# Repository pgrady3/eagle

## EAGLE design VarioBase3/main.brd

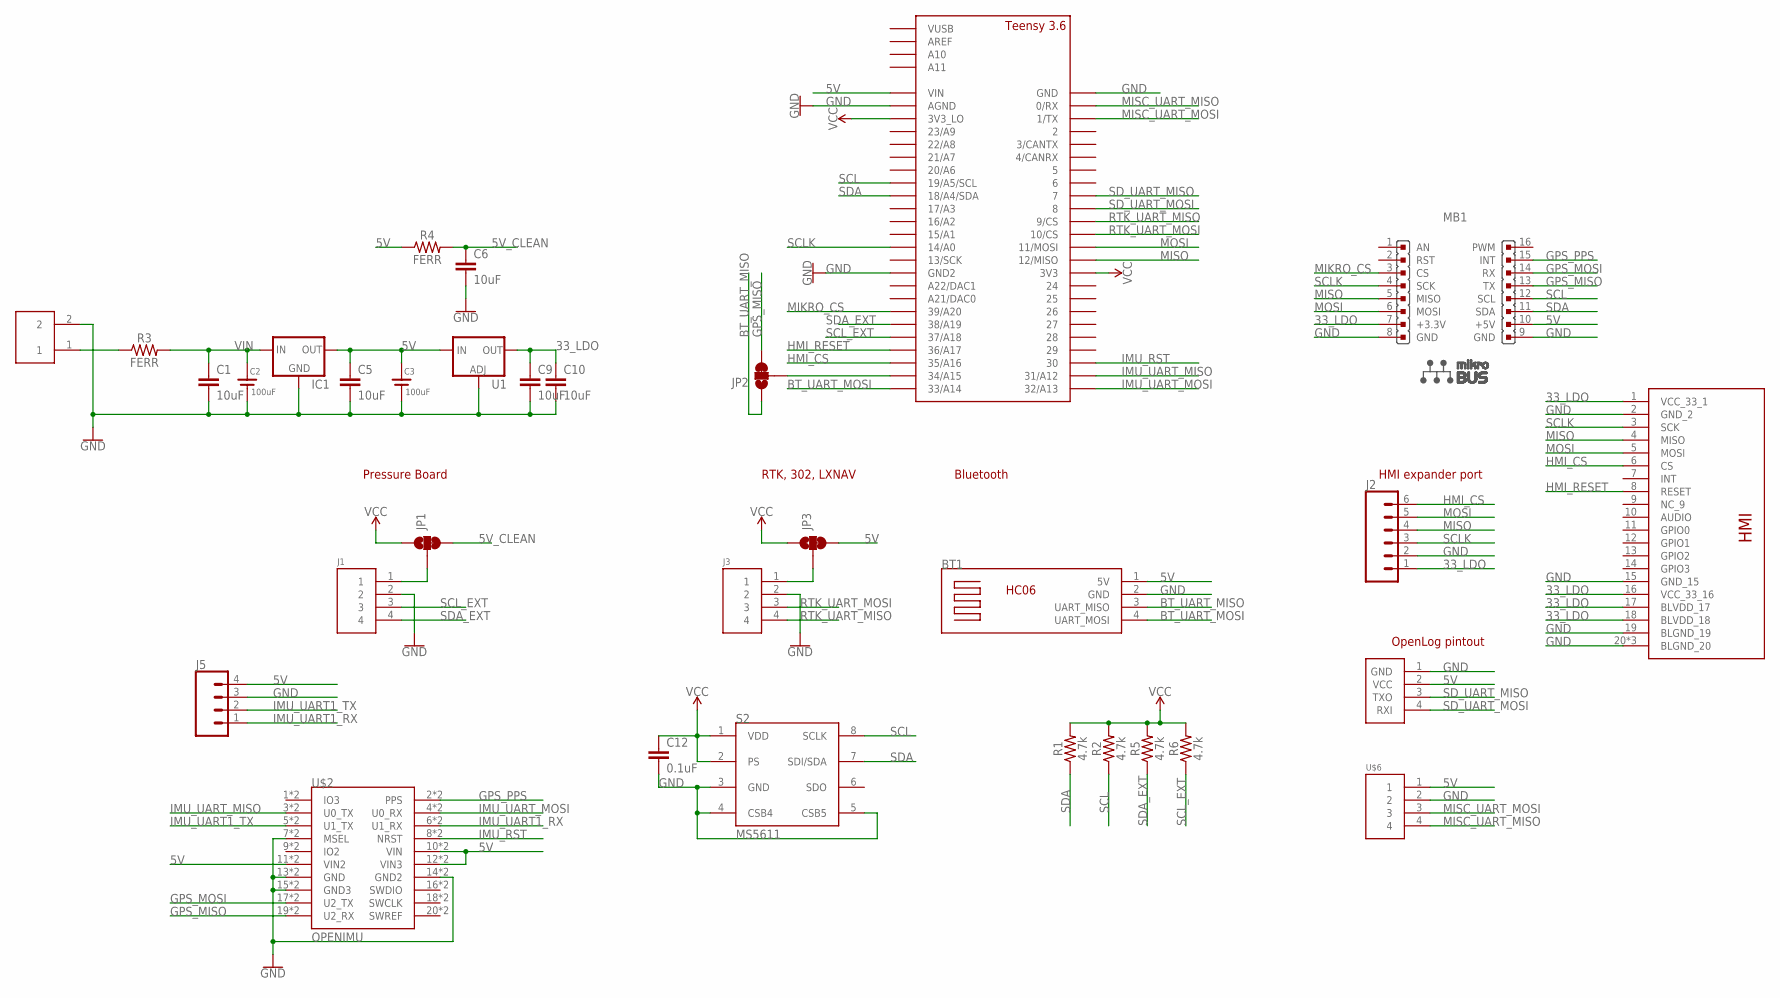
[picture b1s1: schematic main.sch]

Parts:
BT1: HC06
C1, C5, C6, C9, C10: 10uF; 1206
C2, C3: 100uF; CAP_8MM_35MM
C12: 0.1uF; 0603
IC1: V_REG_78XXR-78E; V78W
J1, J3: HEADER4VALULOK; 4PINVALULOK
J2: CONN_06SILK_FEMALE_PTH; 1X06
J5: CONN_04SMD_RA_FEMALE; 1X04_SMD_RA_FEMALE
JP1, JP3: JUMPER-SMT_3_1-NC_TRACE_SILK; SMT-JUMPER_3_1-NC_TRACE_SILK
JP2: JUMPER-SMT_3_1-NC_TRACE_NO-SILK; SMT-JUMPER_3_1-NC_TRACE_NO-SILK
J_PWR: HEADER2; 2PINVALULOK
MB1: MIKROBUS
R1, R2, R5, R6: 4.7k; 0603
R3, R4: FERR; 1206
S2: MS5611
U1: V_REG_317SMD; SOT223
U$1: TEENSY_3.5/3.6_BASIC
U$2: OPENIMU; OPENIMU300ZA
U$4: OPENLOG
U$5: RIVERDI-MATRIX-HMI; FFC-20
U$6: HEADER4VALULOK; 4PINVALULOK

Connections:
5V: BT1.1 (5V), C3.POS (+), C5.1, IC1.OUT, J5.4, JP3.3, MB1.10 (+5V), R4.1, U1.3 (IN), U$1.VIN, U$2.10 (VIN), U$2.11 (VIN2), U$2.12 (VIN3), U$2.H10 (VIN), U$2.H11 (VIN2), U$2.H12 (VIN3), U$4.2 (VCC), U$6.1
5V_CLEAN: C6.1, JP1.3, R4.2
33_LDO: C9.1, C10.1, J2.1, MB1.7 (+3.3V), U1.2 (OUT), U$5.1 (VCC_33_1), U$5.16 (VCC_33_16), U$5.17 (BLVDD_17), U$5.18 (BLVDD_18)
BT_UART_MISO: BT1.3 (UART_MISO), JP2.1
BT_UART_MOSI: BT1.4 (UART_MOSI), U$1.33/A14
GND: BT1.2 (GND), C1.2, C2.NEG (-), C3.NEG (-), C5.2, C6.2, C9.2, C10.2, C12.2, IC1.GND, J1.2, J2.2, J3.2, J5.3, J_PWR.2, MB1.8 (GND), MB1.9 (GND), S2.3 (GND), S2.4 (CSB4), S2.5 (CSB5), U1.1 (ADJ), U$1.AGND, U$1.GND, U$1.GND2, U$2.7 (MSEL), U$2.13 (GND), U$2.14 (GND2), U$2.15 (GND3), U$2.H7 (MSEL), U$2.H13 (GND), U$2.H14 (GND2), U$2.H15 (GND3), U$4.1 (GND), U$5.2 (GND_2), U$5.15 (GND_15), U$5.19 (BLGND_19), U$5.20 (BLGND_20), U$5.PAD1 (BLGND_20), U$5.PAD2 (BLGND_20), U$6.2
GPS_MISO: JP2.3, MB1.13 (TX), U$2.19 (U2_RX), U$2.H19 (U2_RX)
GPS_MOSI: MB1.14 (RX), U$2.17 (U2_TX), U$2.H17 (U2_TX)
GPS_PPS: MB1.15 (INT), U$2.2 (PPS), U$2.H2 (PPS)
HMI_CS: J2.6, U$1.35/A16, U$5.6 (CS)
HMI_RESET: U$1.36/A17, U$5.8 (RESET)
IMU_RST: U$1.30, U$2.8 (NRST), U$2.H8 (NRST)
IMU_UART1_RX: J5.1, U$2.6 (U1_RX), U$2.H6 (U1_RX)
IMU_UART1_TX: J5.2, U$2.5 (U1_TX), U$2.H5 (U1_TX)
IMU_UART_MISO: U$1.31/A12, U$2.3 (U0_TX), U$2.H3 (U0_TX)
IMU_UART_MOSI: U$1.32/A13, U$2.4 (U0_RX), U$2.H4 (U0_RX)
MIKRO_CS: MB1.3 (CS), U$1.39/A20
MISC_UART_MISO: U$1.0/RX, U$6.4
MISC_UART_MOSI: U$1.1/TX, U$6.3
MISO: J2.4, MB1.5 (MISO), U$1.12/MISO, U$5.4 (MISO)
MOSI: J2.5, MB1.6 (MOSI), U$1.11/MOSI, U$5.5 (MOSI)
unnamed: J_PWR.1, R3.1
unnamed: J1.1, JP1.2
unnamed: J3.1, JP3.2
unnamed: JP2.2, U$1.34/A15
RTK_UART_MISO: J3.4, U$1.9/CS
RTK_UART_MOSI: J3.3, U$1.10/CS
SCL: MB1.12 (SCL), R2.1, S2.8 (SCLK), U$1.19/A5/SCL
SCLK: J2.3, MB1.4 (SCK), U$1.14/A0, U$5.3 (SCK)
SCL_EXT: J1.3, R6.1, U$1.37/A18
SDA: MB1.11 (SDA), R1.1, S2.7 (SDI/SDA), U$1.18/A4/SDA
SDA_EXT: J1.4, R5.1, U$1.38/A19
SD_UART_MISO: U$1.7, U$4.3 (TXO)
SD_UART_MOSI: U$1.8, U$4.4 (RXI)
VCC: C12.1, JP1.1, JP3.1, R1.2, R2.2, R5.2, R6.2, S2.1 (VDD), S2.2 (PS), U$1.3V3, U$1.3V3_LO
VIN: C1.1, C2.POS (+), IC1.IN, R3.2

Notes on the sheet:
Pressure Board
RTK, 302, LXNAV
Bluetooth
OpenLog pintout
HMI expander port

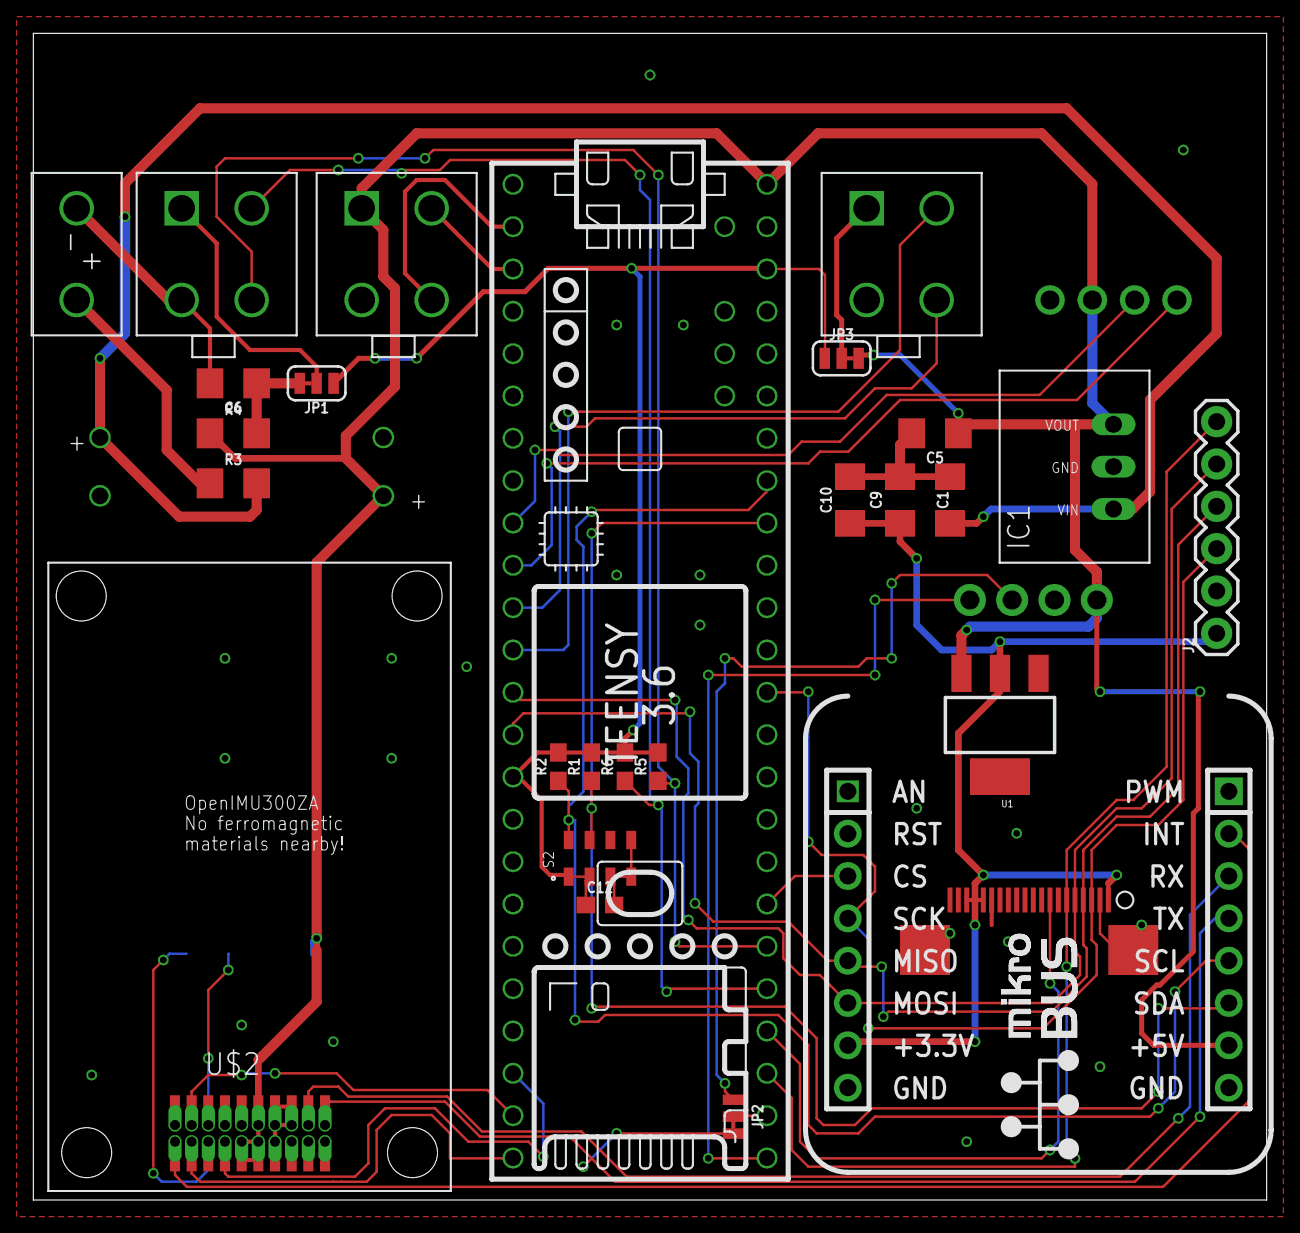
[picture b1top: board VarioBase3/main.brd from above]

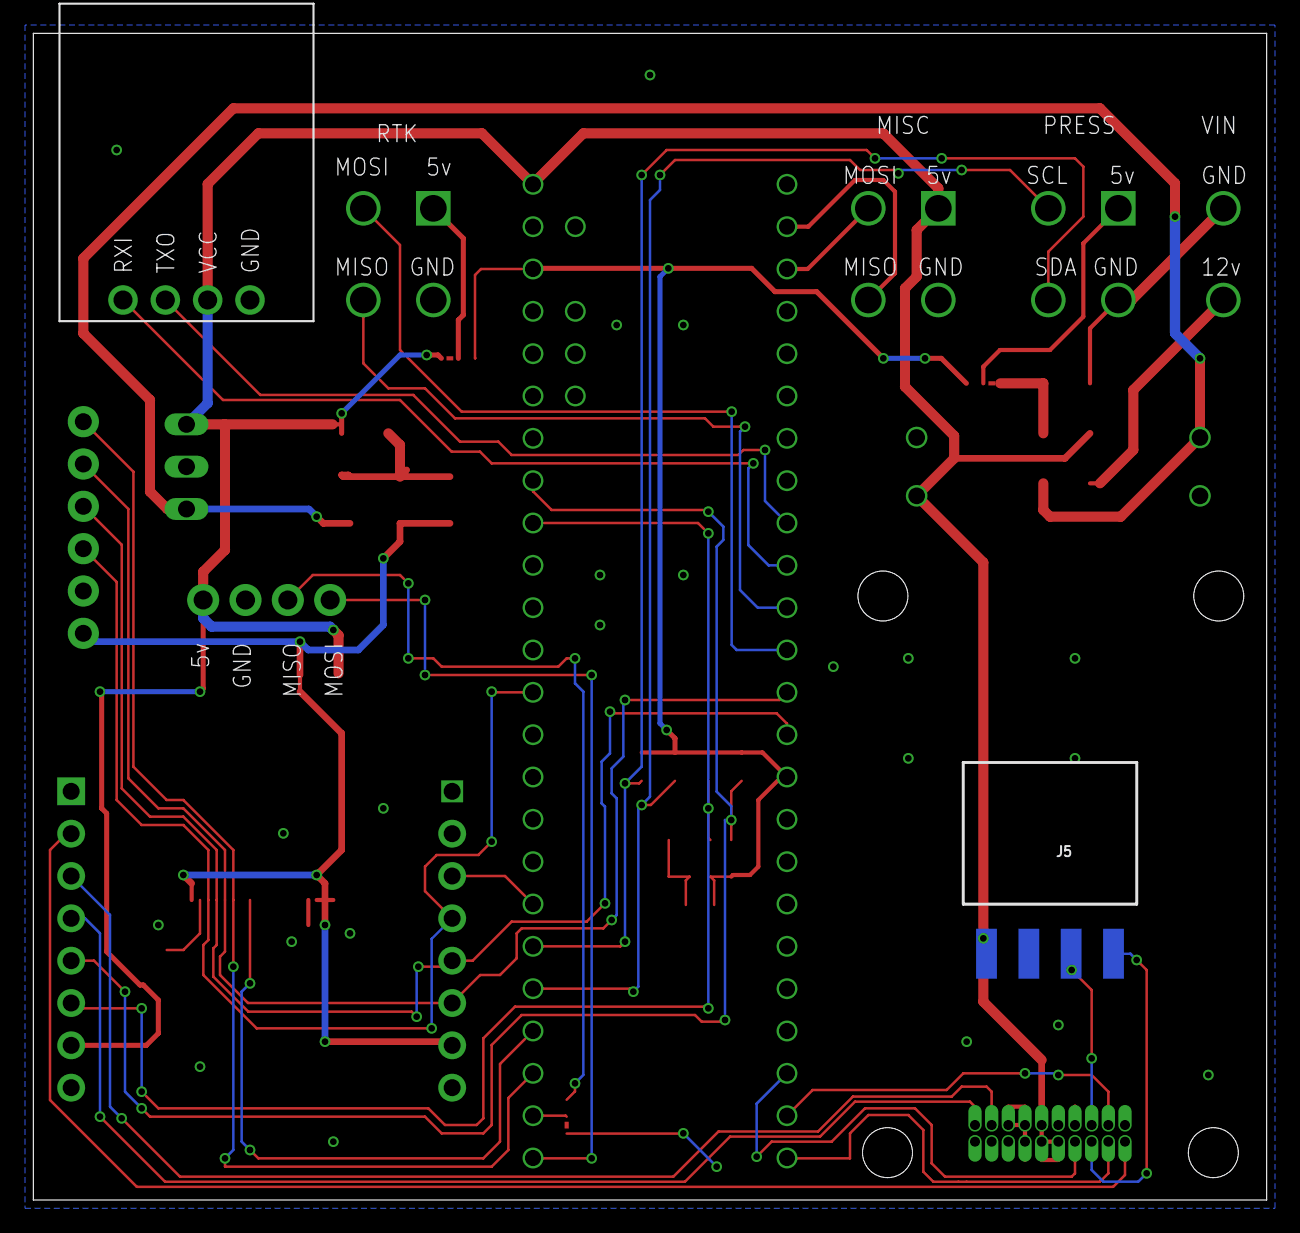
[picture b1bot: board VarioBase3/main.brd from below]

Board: 2 copper layers, 74.0 x 70.0 mm, 32 parts (2 on the bottom side), 36 nets.

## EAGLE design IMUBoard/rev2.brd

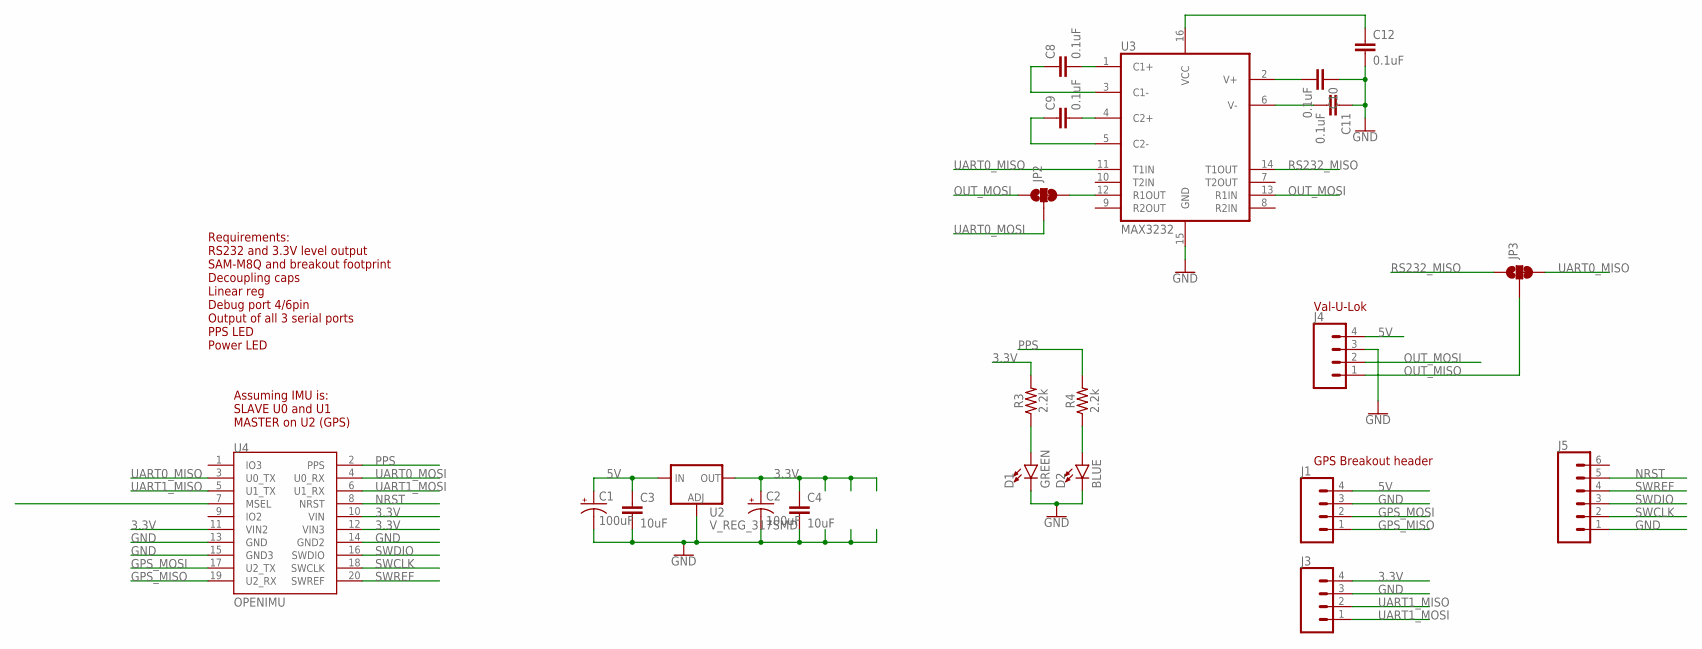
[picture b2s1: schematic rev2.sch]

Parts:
C1, C2: 100uF; EIA3528
C3, C4: 10uF; 0805
C8, C9, C10, C11, C12: 0.1uF; 0603
D1: GREEN; LED-0603
D2: BLUE; LED-0603
J1, J3: CONN_04; 1X04
J4: CONN_04POLAR; MOLEX-1X4
J5: CONN_06POLAR; MOLEX-1X6
JP2, JP3: JUMPER-SMT_3_1-NC_TRACE_SILK; SMT-JUMPER_3_1-NC_TRACE_SILK
R3, R4: 2.2k; 0603
U2: V_REG_317SMD; SOT223
U3: MAX3232; TSSOP16
U4: OPENIMU; OPENIMU300ZA

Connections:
3.3V: C2.A (+), C4.1, J3.4, R3.2, U2.2 (OUT), U4.10 (VIN), U4.11 (VIN2), U4.12 (VIN3)
5V: C1.A (+), C3.1, J1.4, J4.4, U2.3 (IN)
GND: C1.C (-), C2.C (-), C3.2, C4.2, C10.1, C11.1, C12.2, D1.C, D2.C, J1.3, J3.3, J4.3, J5.1, U2.1 (ADJ), U3.15 (GND), U4.13 (GND), U4.14 (GND2), U4.15 (GND3)
GPS_MISO: J1.1, U4.19 (U2_RX)
GPS_MOSI: J1.2, U4.17 (U2_TX)
unnamed: C8.2, U3.1 (C1+)
unnamed: D1.A, R3.1
unnamed: C8.1, U3.3 (C1-)
unnamed: D2.A, R4.1
unnamed: C9.2, U3.4 (C2+)
unnamed: C9.1, U3.5 (C2-)
unnamed: C11.2, U3.6 (V-)
unnamed: C10.2, U3.2 (V+)
unnamed: C12.1, U3.16 (VCC)
unnamed: JP2.3, U3.12 (R1OUT)
NRST: J5.5, U4.8 (NRST)
OUT_MISO: J4.1, JP3.2
OUT_MOSI: J4.2, JP2.1, U3.13 (R1IN)
PPS: R4.2, U4.2 (PPS)
RS232_MISO: JP3.1, U3.14 (T1OUT)
SWCLK: J5.2, U4.18 (SWCLK)
SWDIO: J5.3, U4.16 (SWDIO)
SWREF: J5.4, U4.20 (SWREF)
UART0_MISO: JP3.3, U3.11 (T1IN), U4.3 (U0_TX)
UART0_MOSI: JP2.2, U4.4 (U0_RX)
UART1_MISO: J3.2, U4.5 (U1_TX)
UART1_MOSI: J3.1, U4.6 (U1_RX)

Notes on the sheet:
Requirements: RS232 and 3.3V level output SAM-M8Q and breakout footprint Decoupling caps Linear reg Debug port 4/6pin Output of all 3 serial ports PPS LED Power LED
Val-U-Lok
Assuming IMU is: SLAVE U0 and U1 MASTER on U2 (GPS)
GPS Breakout header

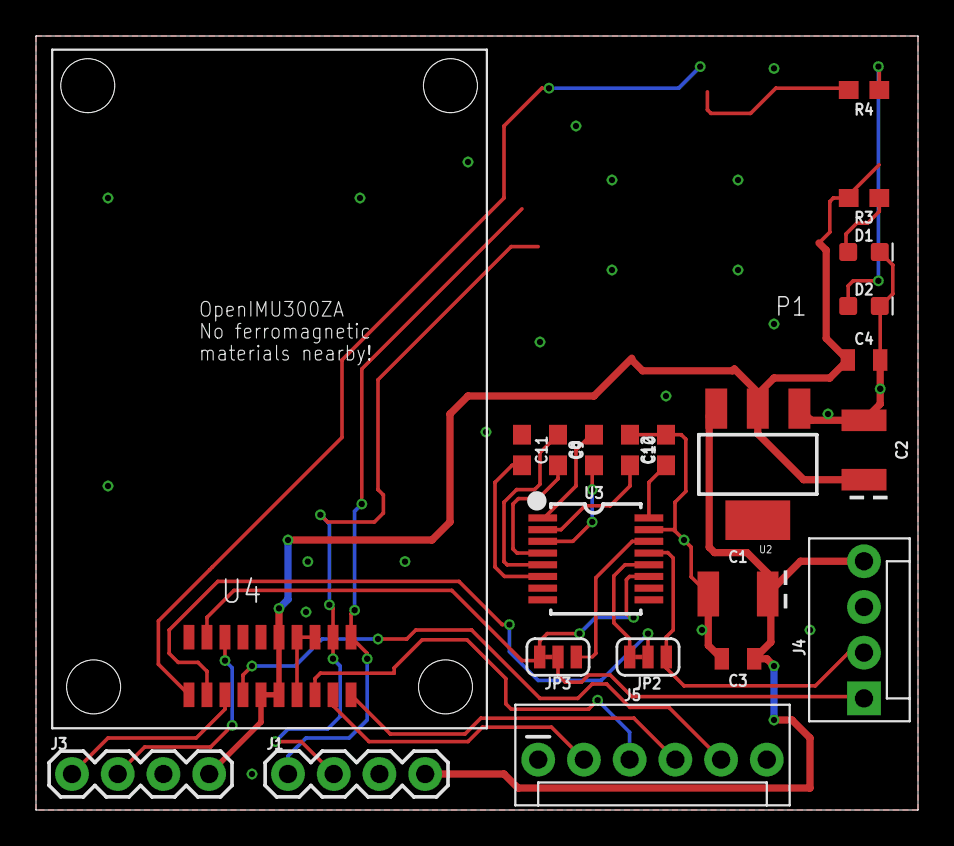
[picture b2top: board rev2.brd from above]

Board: 2 copper layers, 49.0 x 43.0 mm, 22 parts (0 on the bottom side), 27 nets.

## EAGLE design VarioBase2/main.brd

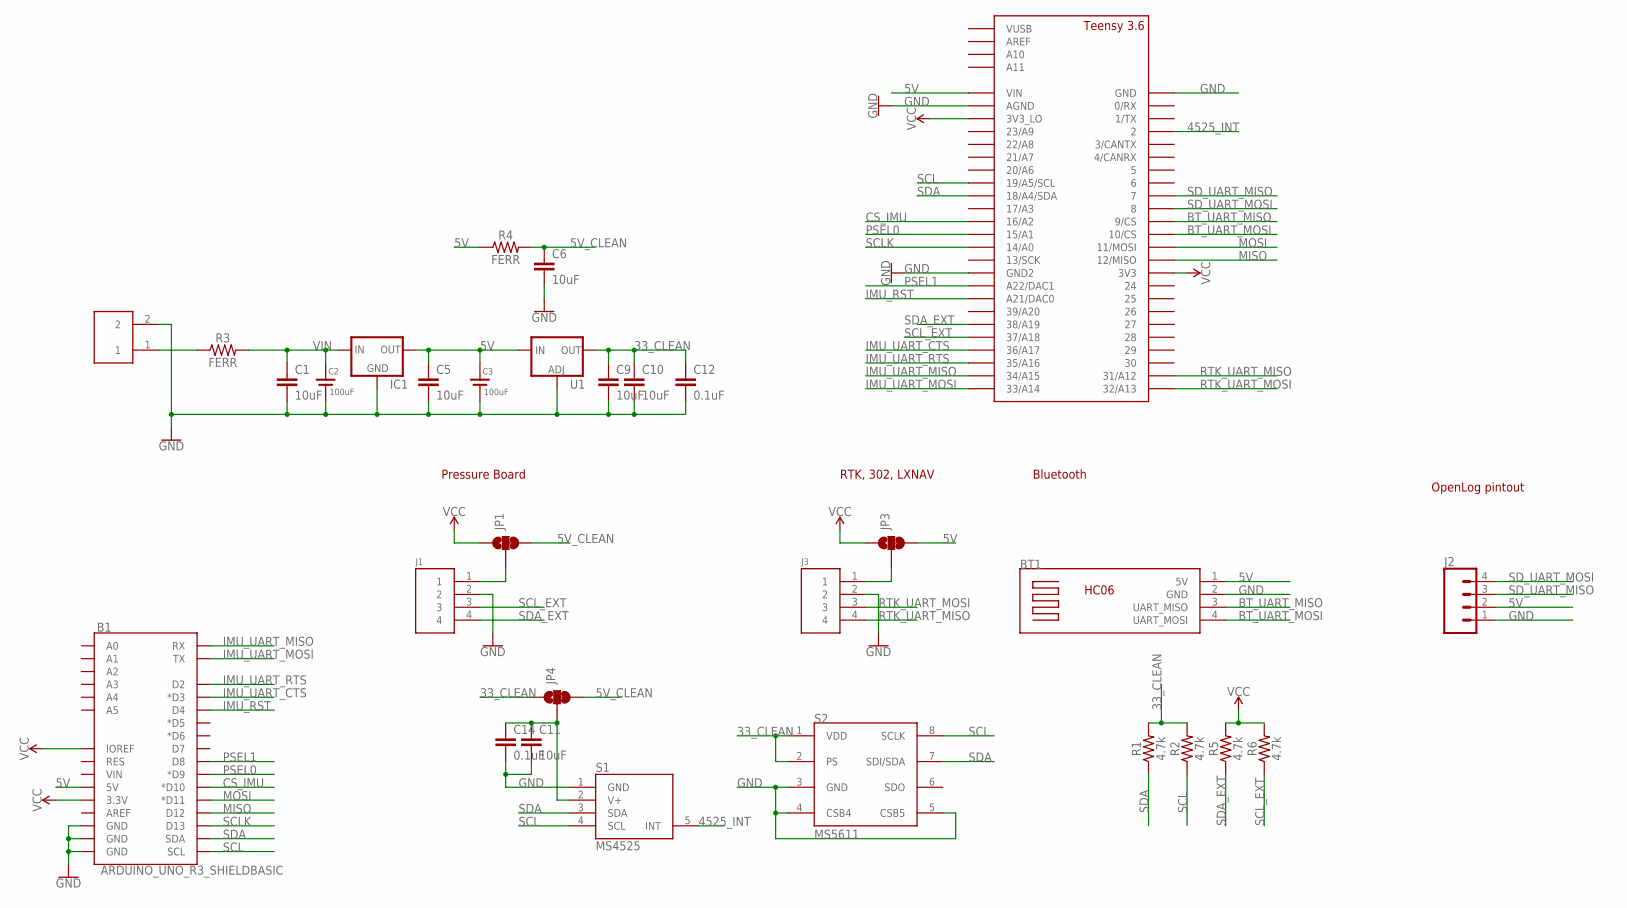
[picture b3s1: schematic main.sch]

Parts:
B1: ARDUINO_UNO_R3_SHIELDBASIC; UNO_R3_SHIELD
BT1: HC06
C1, C5, C6, C9, C10, C11: 10uF; 1206
C2, C3: 100uF; CAP_8MM_35MM
C12, C14: 0.1uF; 0603
IC1: V_REG_78XXR-78E; V78W
J1, J3: HEADER4VALULOK; 4PINVALULOK
J2: CONN_04; 1X04
JP1, JP3, JP4: JUMPER-SMT_3_1-NC_TRACE_SILK; SMT-JUMPER_3_1-NC_TRACE_SILK
R1, R2, R5, R6: 4.7k; 0603
R3, R4: FERR; 1206
S1: MS4525; DIP1270W53P254L990H762Q8B
S2: MS5611
U1: V_REG_317SMD; SOT223
U$1: TEENSY_3.5/3.6_BASIC
U$3: HEADER2; 2PINVALULOK

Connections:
5V: B1.5V, BT1.1 (5V), C3.POS (+), C5.1, IC1.OUT, J2.2, JP3.3, R4.1, U1.3 (IN), U$1.VIN
5V_CLEAN: C6.1, JP1.3, JP4.3, R4.2
33_CLEAN: C9.1, C10.1, C12.1, JP4.1, R1.2, R2.2, S2.1 (VDD), S2.2 (PS), U1.2 (OUT)
4525_INT: S1.5 (INT), U$1.2
BT_UART_MISO: BT1.3 (UART_MISO), U$1.9/CS
BT_UART_MOSI: BT1.4 (UART_MOSI), U$1.10/CS
CS_IMU: B1.D10 (*D10), U$1.16/A2
GND: B1.GND@0 (GND), B1.GND@1 (GND), B1.GND@2 (GND), BT1.2 (GND), C1.2, C2.NEG (-), C3.NEG (-), C5.2, C6.2, C9.2, C10.2, C11.2, C12.2, C14.2, IC1.GND, J1.2, J2.1, J3.2, S1.1 (GND), S2.3 (GND), S2.4 (CSB4), S2.5 (CSB5), U1.1 (ADJ), U$1.AGND, U$1.GND, U$1.GND2, U$3.2
IMU_RST: B1.D4, U$1.21/DAC0 (A21/DAC0)
IMU_UART_CTS: B1.D3 (*D3), U$1.36/A17
IMU_UART_MISO: B1.RX, U$1.34/A15
IMU_UART_MOSI: B1.TX, U$1.33/A14
IMU_UART_RTS: B1.D2, U$1.35/A16
MISO: B1.D12, U$1.12/MISO
MOSI: B1.D11 (*D11), U$1.11/MOSI
unnamed: R3.1, U$3.1
unnamed: J1.1, JP1.2
unnamed: J3.1, JP3.2
unnamed: C11.1, C14.1, JP4.2, S1.2 (V+)
PSEL0: B1.D9 (*D9), U$1.15/A1
PSEL1: B1.D8, U$1.A22/DAC1
RTK_UART_MISO: J3.4, U$1.31/A12
RTK_UART_MOSI: J3.3, U$1.32/A13
SCL: B1.SCL, R2.1, S1.4 (SCL), S2.8 (SCLK), U$1.19/A5/SCL
SCLK: B1.D13, U$1.14/A0
SCL_EXT: J1.3, R6.1, U$1.37/A18
SDA: B1.SDA, R1.1, S1.3 (SDA), S2.7 (SDI/SDA), U$1.18/A4/SDA
SDA_EXT: J1.4, R5.1, U$1.38/A19
SD_UART_MISO: J2.3, U$1.7
SD_UART_MOSI: J2.4, U$1.8
VCC: B1.3.3V, B1.IOREF, JP1.1, JP3.1, R5.2, R6.2, U$1.3V3, U$1.3V3_LO
VIN: C1.1, C2.POS (+), IC1.IN, R3.2

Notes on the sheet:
Pressure Board
RTK, 302, LXNAV
Bluetooth
OpenLog pintout

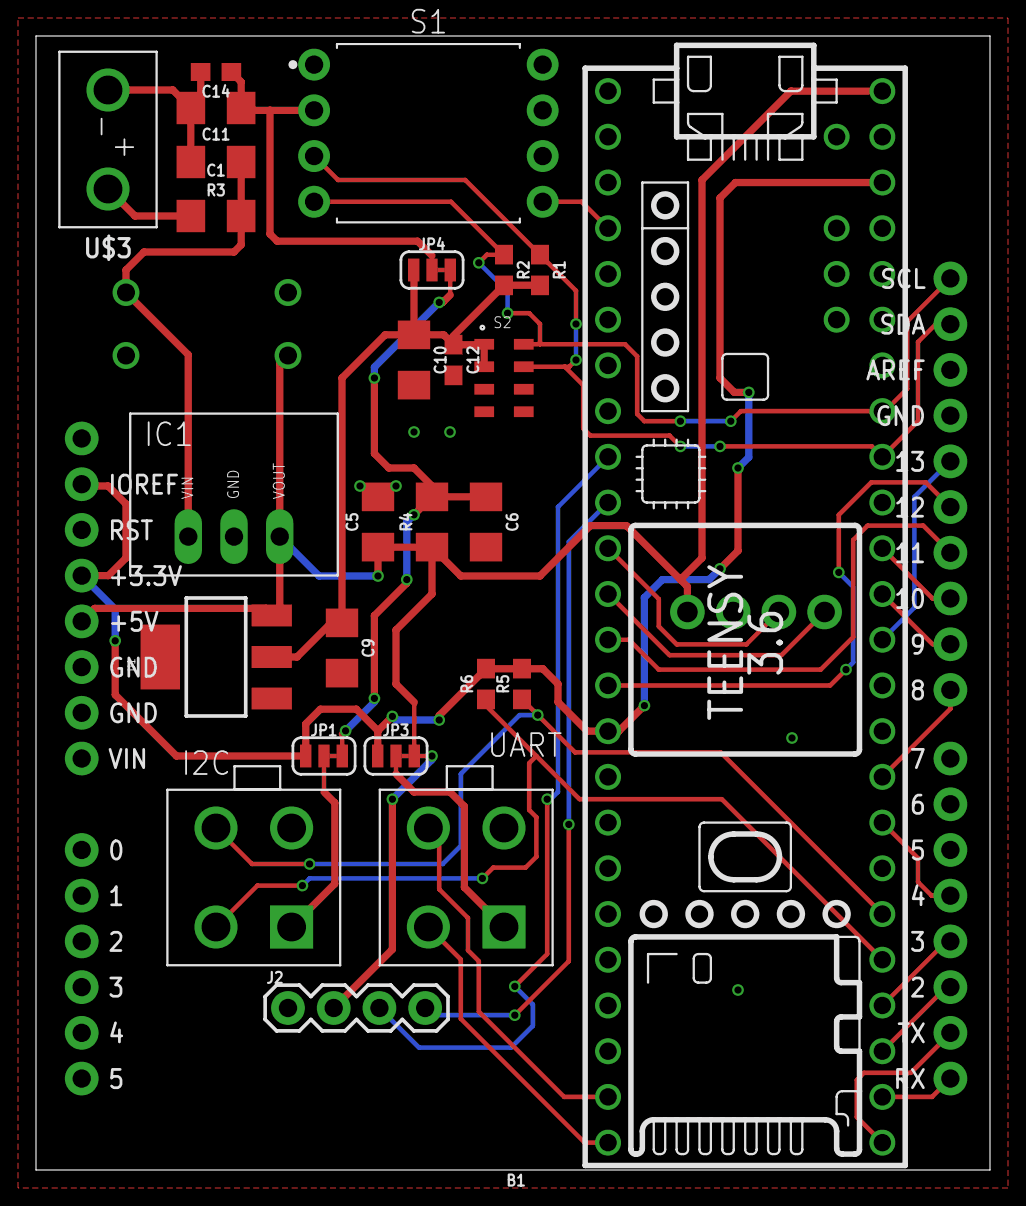
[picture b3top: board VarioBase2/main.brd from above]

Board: 2 copper layers, 53.0 x 63.0 mm, 30 parts (1 on the bottom side), 32 nets.

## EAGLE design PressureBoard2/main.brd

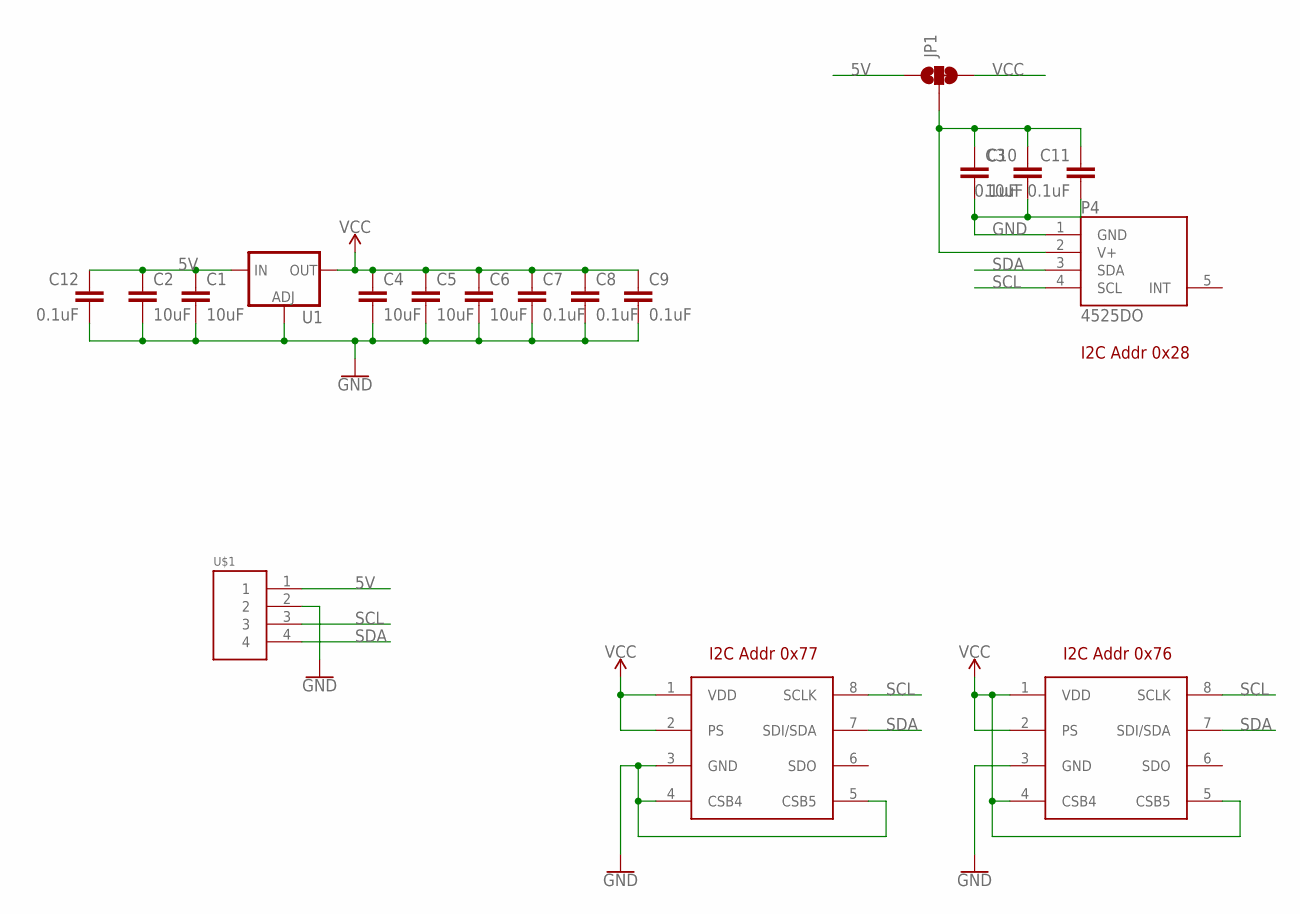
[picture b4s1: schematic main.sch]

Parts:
C1, C2, C3, C4, C5, C6: 10uF; 0805
C7, C8, C9, C10, C11, C12: 0.1uF; 0603
JP1: JUMPER-SMT_3_1-NC_TRACE_NO-SILK; SMT-JUMPER_3_1-NC_TRACE_NO-SILK
P1, P2: MS5611
P4: 4525DO; DIP1270W53P254L990H762Q8B
U1: V_REG_317SMD; SOT223
U$1: HEADER4VALULOK; 4PINVALULOK

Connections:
5V: C1.1, C2.1, C12.1, JP1.1, U1.3 (IN), U$1.1
GND: C1.2, C2.2, C3.2, C4.2, C5.2, C6.2, C7.2, C8.2, C9.2, C10.2, C11.2, C12.2, P1.3 (GND), P1.4 (CSB4), P1.5 (CSB5), P2.3 (GND), P4.1 (GND), U1.1 (ADJ), U$1.2
unnamed: C3.1, C10.1, C11.1, JP1.2, P4.2 (V+)
SCL: P1.8 (SCLK), P2.8 (SCLK), P4.4 (SCL), U$1.3
SDA: P1.7 (SDI/SDA), P2.7 (SDI/SDA), P4.3 (SDA), U$1.4
VCC: C4.1, C5.1, C6.1, C7.1, C8.1, C9.1, JP1.3, P1.1 (VDD), P1.2 (PS), P2.1 (VDD), P2.2 (PS), P2.4 (CSB4), P2.5 (CSB5), U1.2 (OUT)

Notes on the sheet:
I2C Addr 0x28
I2C Addr 0x77
I2C Addr 0x76

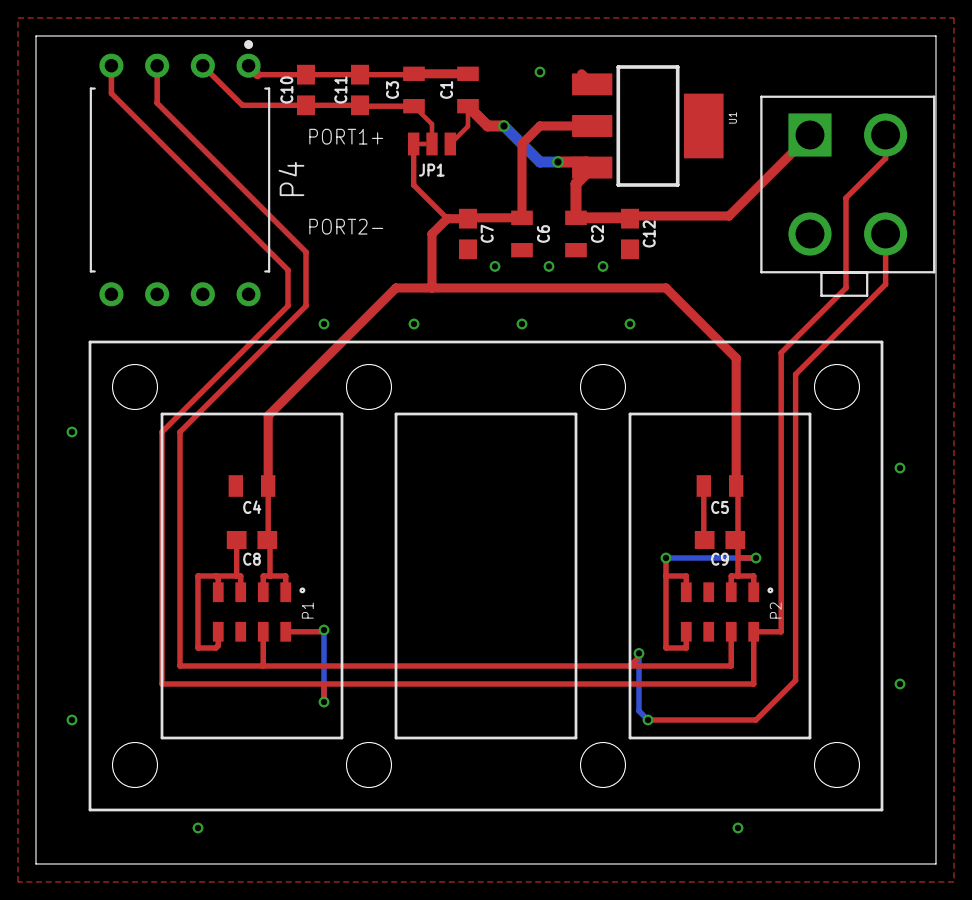
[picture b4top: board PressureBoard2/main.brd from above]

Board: 2 copper layers, 50.0 x 46.0 mm, 18 parts (0 on the bottom side), 6 nets.

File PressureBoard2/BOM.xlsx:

Digikey part # | Designator | Qty | Price | Description
AZ1117EH-3.3TRG1DICT-ND | U1 | 1 | 0.32 | Linear 3.3 reg |  |  |  | 0.32 |  | 64.25
1276-6455-1-ND | C1,C2,C3,C4,C5,C6 | 6 | 0.1 | 10uF cap |  |  |  | 0.60000000000000009
1276-1000-1-ND | C7,C8,C9 | 3 | 0.01 | 0.1uF cap |  |  |  | 0.03
2057-ICS-308-T-ND |  |  |  | 8 DIP socket |  |  |  | 0
223-1622-1-ND |  | 2 | 12.4 | MS5611 |  |  |  | 24.8
223-1110-ND |  | 1 | 38.5 | 4525DO |  |  |  | 38.5
 |  |  |  |  |  |  |  | 0
EB50 |  | 3 |  | 3/16 to 10-32 conn |  |  |  | 0
EB25 |  | 2 |  | 3/32 to 10-32 conn |  |  |  | 0
 |  |  |  |  |  |  |  | 0
 |  |  |  |  |  |  |  | 0
 |  |  |  |  |  |  |  | 0
 |  |  |  |  |  |  |  | 0
 |  |  |  |  |  |  |  | 0
 |  |  |  |  |  |  |  | 0
 |  |  |  |  |  |  |  | 0
 |  |  |  |  |  |  |  | 0
 |  |  |  |  |  |  |  | 0

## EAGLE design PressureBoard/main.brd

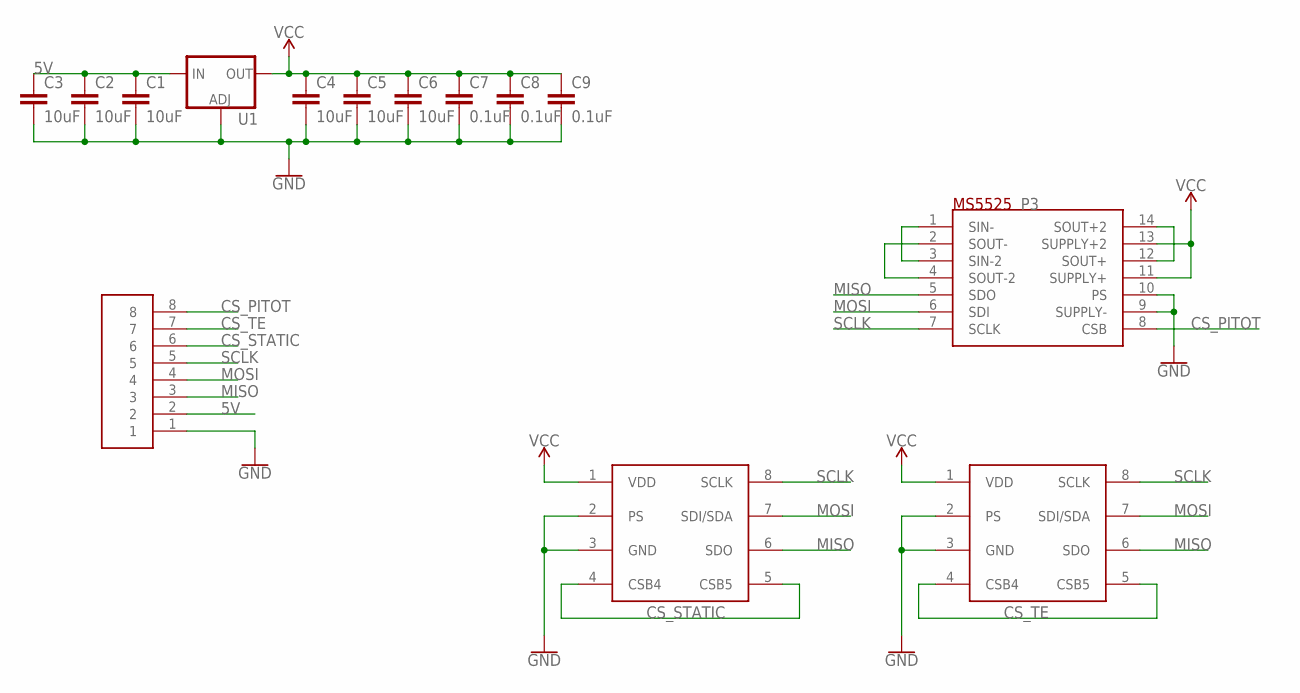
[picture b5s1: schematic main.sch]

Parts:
C1, C2, C3, C4, C5, C6: 10uF; 0805
C7, C8, C9: 0.1uF; 0603
P1, P2: MS5611
P3: MS5525; SOIC14-WIDE
U1: V_REG_317SMD; SOT223
U$1: HEADER8; 8PINVALULOK

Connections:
5V: C1.1, C2.1, C3.1, U1.3 (IN), U$1.2
CS_PITOT: P3.8 (CSB), U$1.8
CS_STATIC: P1.4 (CSB4), P1.5 (CSB5), U$1.6
CS_TE: P2.4 (CSB4), P2.5 (CSB5), U$1.7
GND: C1.2, C2.2, C3.2, C4.2, C5.2, C6.2, C7.2, C8.2, C9.2, P1.2 (PS), P1.3 (GND), P2.2 (PS), P2.3 (GND), P3.9 (SUPPLY-), P3.10 (PS), U1.1 (ADJ), U$1.1
MISO: P1.6 (SDO), P2.6 (SDO), P3.5 (SDO), U$1.3
MOSI: P1.7 (SDI/SDA), P2.7 (SDI/SDA), P3.6 (SDI), U$1.4
unnamed: P3.1 (SIN-), P3.3 (SIN-2)
unnamed: P3.2 (SOUT-), P3.4 (SOUT-2)
unnamed: P3.12 (SOUT+), P3.14 (SOUT+2)
SCLK: P1.8 (SCLK), P2.8 (SCLK), P3.7 (SCLK), U$1.5
VCC: C4.1, C5.1, C6.1, C7.1, C8.1, C9.1, P1.1 (VDD), P2.1 (VDD), P3.11 (SUPPLY+), P3.13 (SUPPLY+2), U1.2 (OUT)

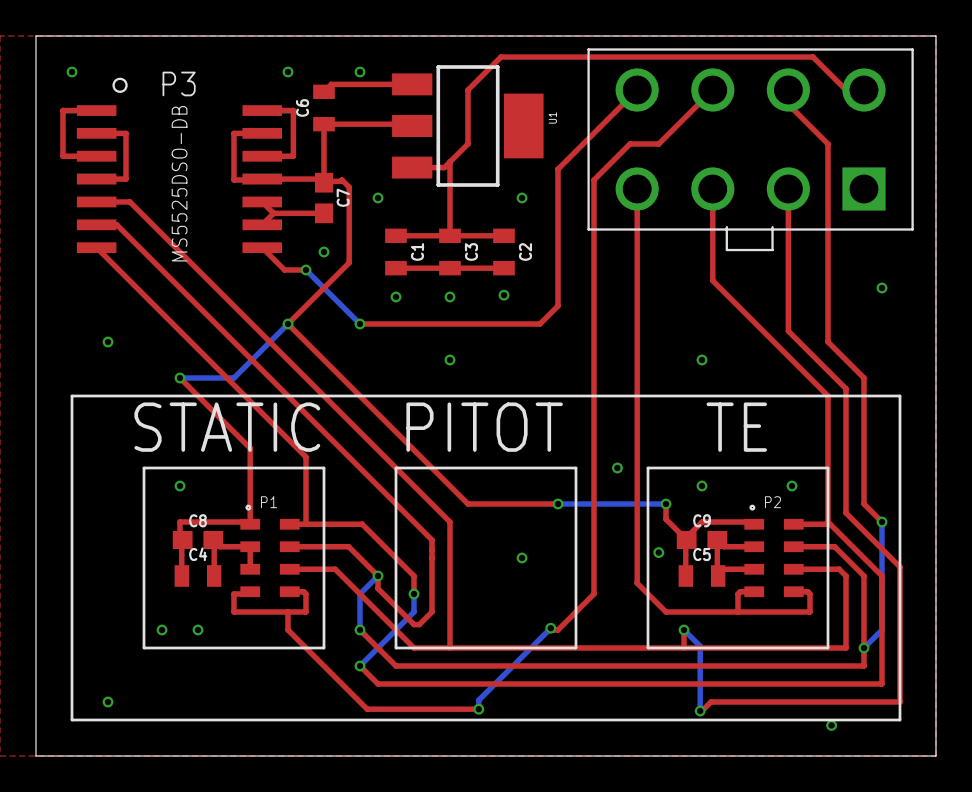
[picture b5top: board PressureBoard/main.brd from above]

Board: 2 copper layers, 50.0 x 40.0 mm, 14 parts (0 on the bottom side), 12 nets.

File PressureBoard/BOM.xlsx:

Digikey part # | Designator | Qty | Price | Description
AZ1117EH-3.3TRG1DICT-ND | U1 | 1 | 0.32 | Linear 3.3 reg |  |  |  | 0.32 |  | 0.95000000000000018
1276-6455-1-ND | C1,C2,C3,C4,C5,C6 | 6 | 0.1 | 10uF cap |  |  |  | 0.60000000000000009
1276-1000-1-ND | C7,C8,C9 | 3 | 0.01 | 0.1uF cap |  |  |  | 0.03
 |  |  |  |  |  |  |  | 0
 |  |  |  |  |  |  |  | 0
 |  |  |  |  |  |  |  | 0
 |  |  |  |  |  |  |  | 0
 |  |  |  |  |  |  |  | 0
 |  |  |  |  |  |  |  | 0
 |  |  |  |  |  |  |  | 0
 |  |  |  |  |  |  |  | 0
 |  |  |  |  |  |  |  | 0
 |  |  |  |  |  |  |  | 0
 |  |  |  |  |  |  |  | 0
 |  |  |  |  |  |  |  | 0
 |  |  |  |  |  |  |  | 0

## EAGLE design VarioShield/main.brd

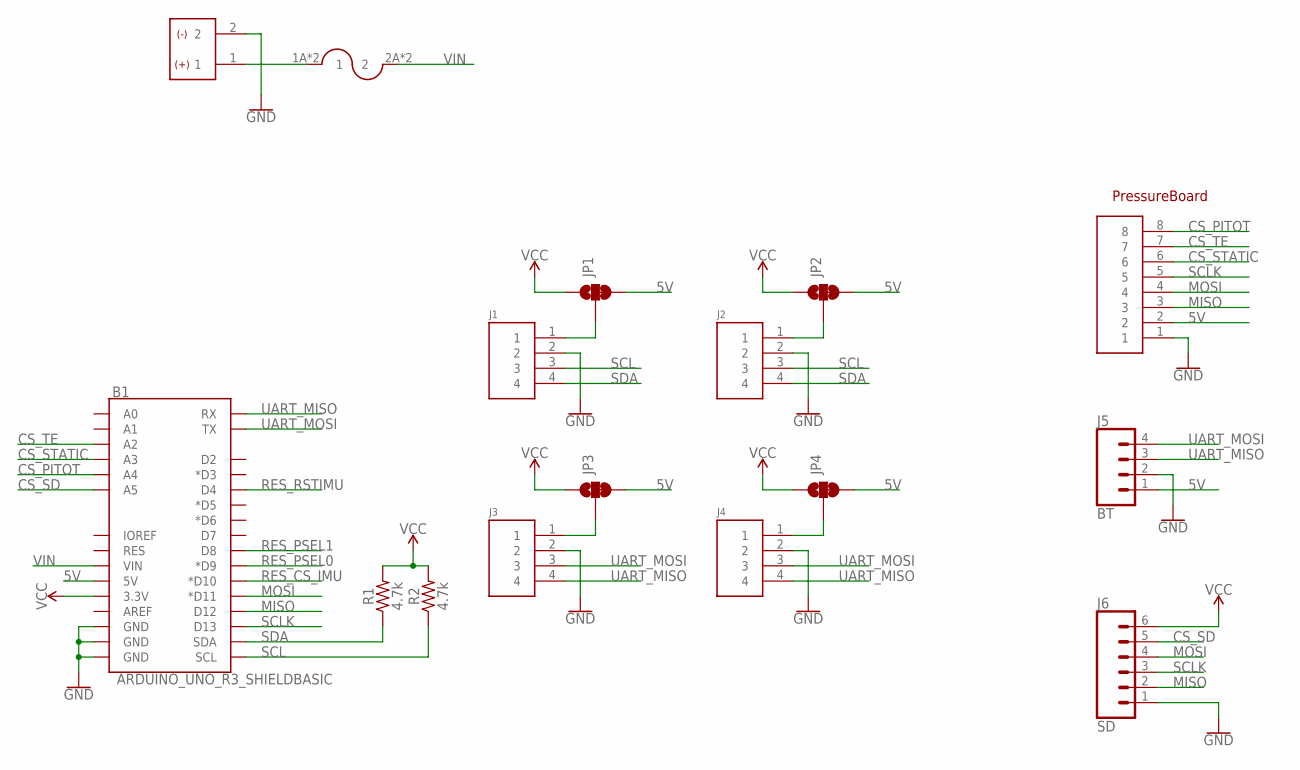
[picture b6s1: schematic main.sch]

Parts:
B1: ARDUINO_UNO_R3_SHIELDBASIC; UNO_R3_SHIELD
J1, J2, J3, J4: HEADER4VALULOK; 4PINVALULOK
J5: BT; 1X04_NO_SILK
J6: SD; 1X06_NO_SILK
JP1, JP2, JP3, JP4: JUMPER-SMT_3_1-NC_TRACE_SILK; SMT-JUMPER_3_1-NC_TRACE_SILK
R1, R2: 4.7k; 0603
U$1: PB; 8PINVALULOK
U$2: FUSE; AUTO_FUSE
U$3: HEADER2; 2PINVALULOK

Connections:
5V: B1.5V, J5.1, JP1.3, JP2.3, JP3.3, JP4.3, U$1.2
CS_PITOT: B1.A4, U$1.8
CS_SD: B1.A5, J6.5
CS_STATIC: B1.A3, U$1.6
CS_TE: B1.A2, U$1.7
GND: B1.GND@0 (GND), B1.GND@1 (GND), B1.GND@2 (GND), J1.2, J2.2, J3.2, J4.2, J5.2, J6.1, U$1.1, U$3.2
MISO: B1.D12, J6.2, U$1.3
MOSI: B1.D11 (*D11), J6.4, U$1.4
unnamed: J2.1, JP2.2
unnamed: J1.1, JP1.2
unnamed: J3.1, JP3.2
unnamed: J4.1, JP4.2
unnamed: U$2.1A (1), U$2.1B (1), U$3.1
RES_CS_IMU: B1.D10 (*D10)
RES_PSEL0: B1.D9 (*D9)
RES_PSEL1: B1.D8
RES_RSTIMU: B1.D4
SCL: B1.SCL, J1.3, J2.3, R2.1
SCLK: B1.D13, J6.3, U$1.5
SDA: B1.SDA, J1.4, J2.4, R1.1
UART_MISO: B1.RX, J3.4, J4.4, J5.3
UART_MOSI: B1.TX, J3.3, J4.3, J5.4
VCC: B1.3.3V, J6.6, JP1.1, JP2.1, JP3.1, JP4.1, R1.2, R2.2
VIN: B1.VIN, U$2.2A (2), U$2.2B (2)

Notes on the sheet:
PressureBoard

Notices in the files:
parts and their libraries:
SparkFun-DigitalIC: Licensing: CC v3.0 Share-Alike You are welcome to use this library for commercial purposes.
SparkFun-Capacitors: Licensing: Creative Commons ShareAlike 4.0 International - https://creativecommons.org/licenses/by-sa/4.0
